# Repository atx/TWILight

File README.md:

TWILight
========

VGA-I2C Breakout board with few LEDs and Atmega. The footprint libraries used are the ones by [oshec](http://library.oshec.org/) and [Dangerous 
Prototypes](http://dangerousprototypes.com/2012/09/18/eagle-parts-our-eagle-library-converted-to-kicad/).

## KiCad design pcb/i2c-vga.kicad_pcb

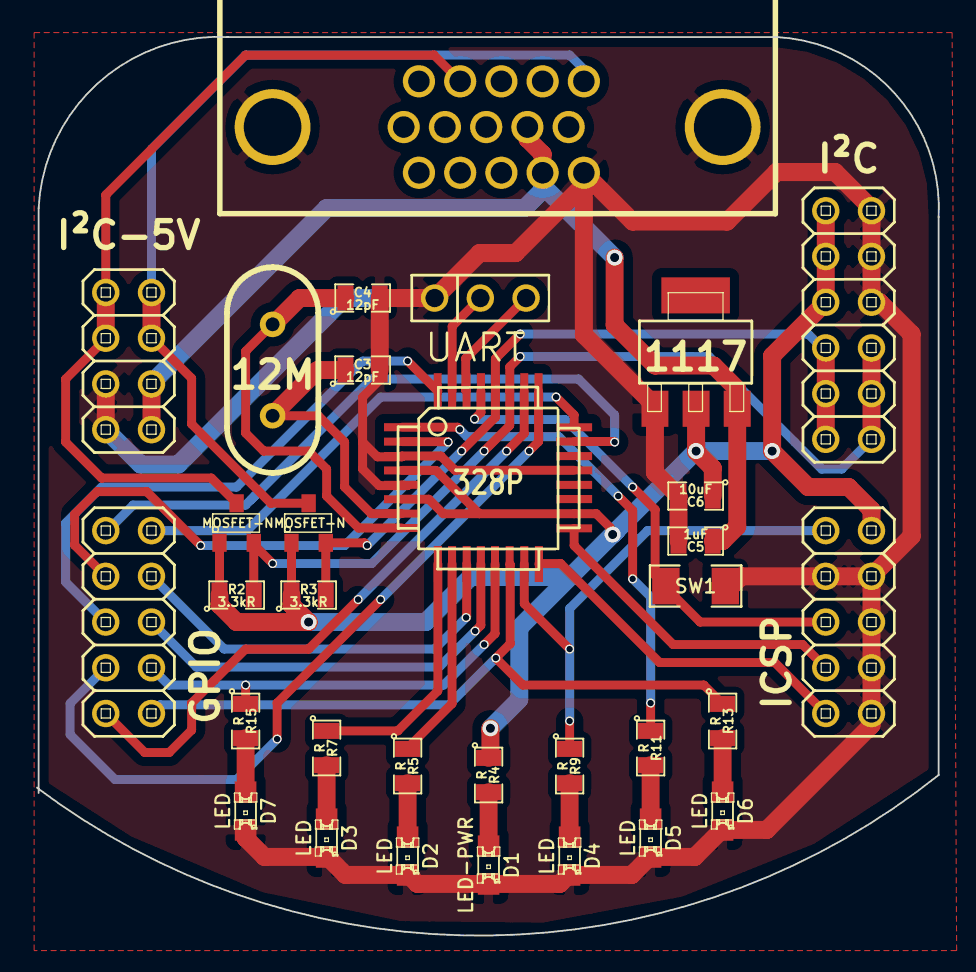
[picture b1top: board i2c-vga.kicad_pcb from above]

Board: 2 copper layers, 50.1 x 49.9 mm, 21 parts (0 on the bottom side), 9 nets.

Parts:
C3, C4: 12pF; SM0805
C5: 1uF; SM0805
C6: 10uF; SM0805
D1: LED-PWR; LED-0805
D2, D3, D4, D5, D6, D7: LED; LED-0805
R2, R3: 3.3kR; SM0805
R4, R5, R7, R9, R11, R13, R15: R; SM0805
SW1: SPST; SM1206

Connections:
+3.3V: C6.1, R2.1, R3.1, R4.1
GND: C3.2, C4.2, C5.2, C6.2, D1.2, D2.2, D3.2, D4.2, D5.2, D6.2, D7.2, SW1.1
unnamed: D2.1, R5.2
unnamed: D7.1, R15.2
unnamed: D1.1, R4.2
unnamed: D3.1, R7.2
unnamed: D6.1, R13.2
unnamed: D5.1, R11.2
unnamed: D4.1, R9.2

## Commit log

2014-05-15 Created directory structure.
2014-05-15 Added KiCAD PCB sources.
2014-05-18 Added firmware for the ATmega.
2014-05-18 Removed commented out printf in avr/main.c
2014-06-11 Added correct libraries to pcb/libs. KiCad project does no longer require the entire oshec library.
2014-06-11 AVR FW now disables PWM when the compare register is set to zero. Even when the OCR register is zero, AVR in fast PWM mode produces short voltage bursts, so the LEDs were not dimmed properly.
2014-06-11 Set F_CPU in Makefile to match the value on the schematic (12 MHz).
2014-06-14 Reworked the AVR I2C GPIO interface. Now we have atomic access to GPIO pins. Also this greatly simplifies driver code.
2014-06-15 Added Linux kernel driver.
2014-06-15 Removed TODO list as all items are finished.
2014-06-16 Changed LED colors in source to match the ones on board.
2014-06-19 Added GPL3 license headers to avr/main.c
2014-06-19 PWM now does not automatically start on reset.
    This means the LEDs are now properly turned off on power up.
2014-06-22 Added rendered PDF file schematic
